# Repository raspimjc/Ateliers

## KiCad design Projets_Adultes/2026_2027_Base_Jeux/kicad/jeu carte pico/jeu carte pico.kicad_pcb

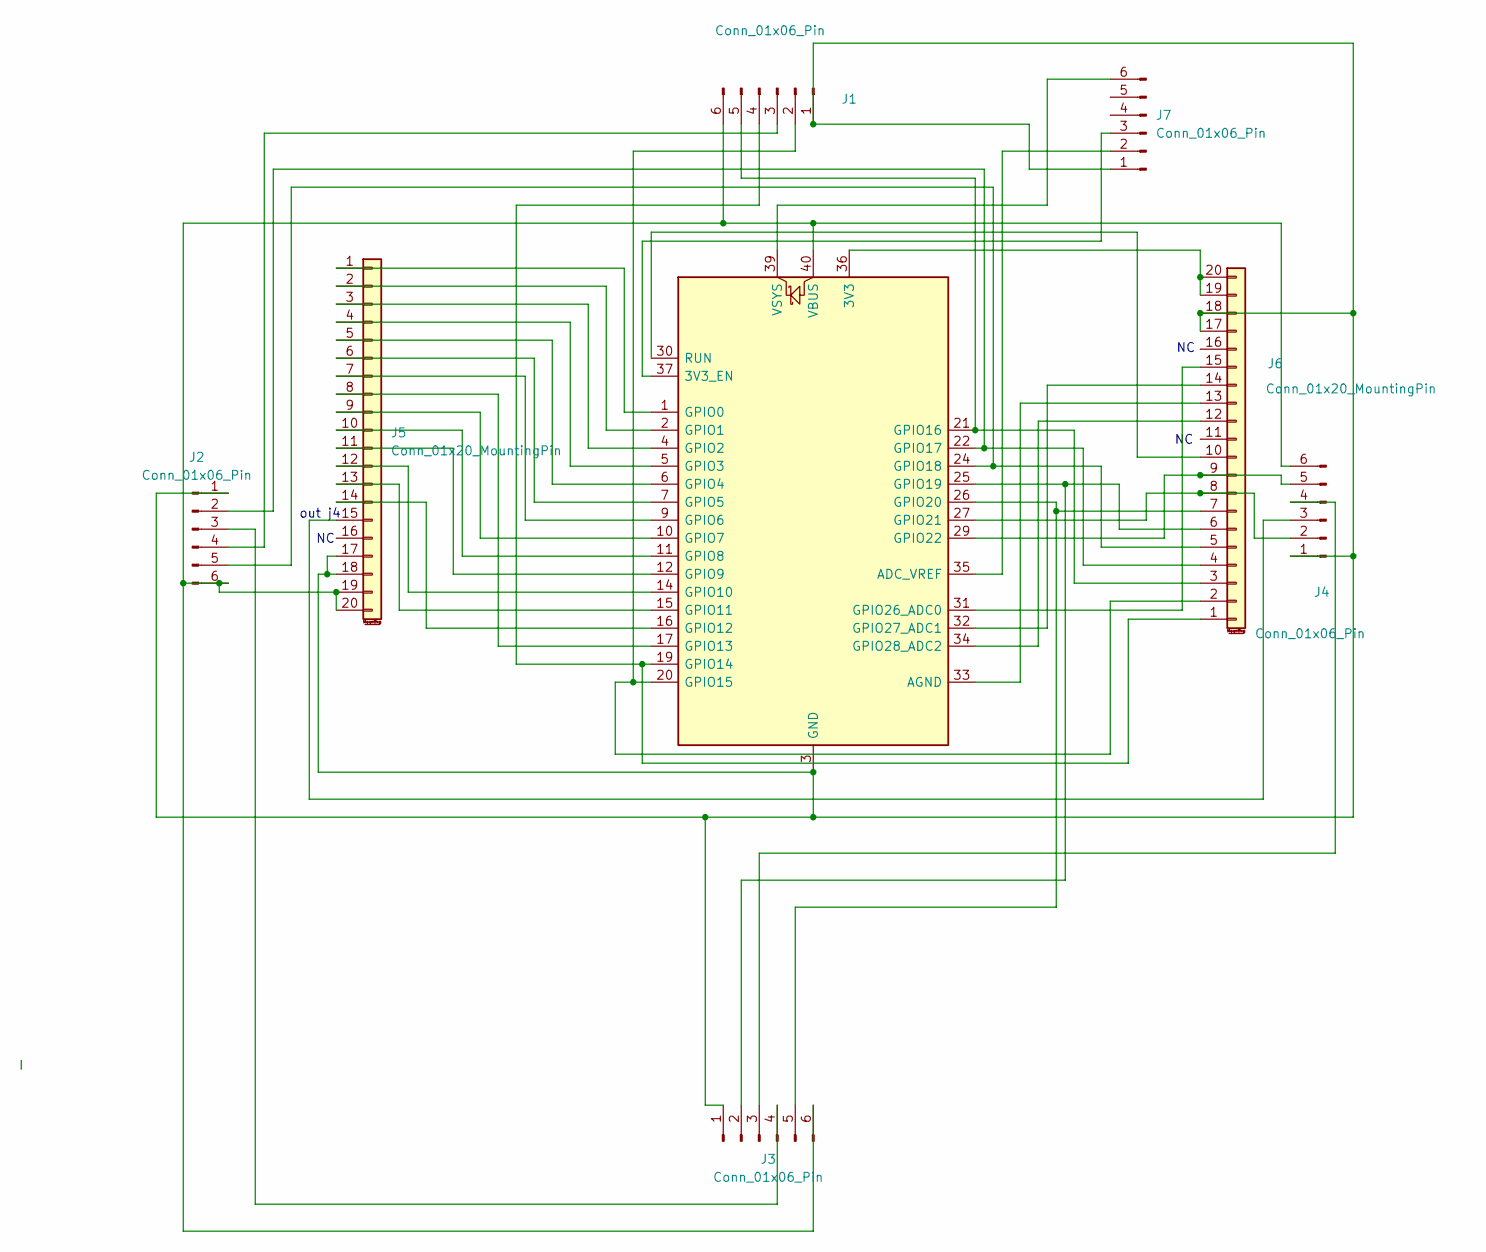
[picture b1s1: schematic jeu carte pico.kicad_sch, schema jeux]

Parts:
A1: RaspberryPi_Pico; Pico_Common_THT
J1, J2, J3, J4, J7: Conn_01x06_Pin; JST_XH_B6B-XH-A_1x06_P2.50mm_Vertical
J5, J6: Conn_01x20_MountingPin

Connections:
unnamed: A1.36 (3V3), J6.19 (Pin_2), J6.20 (Pin_1)
unnamed: A1.37 (3V3_EN), J7.3
unnamed: A1.35 (ADC_VREF), J7.2
unnamed: A1.33 (AGND), J6.13 (Pin_8)
unnamed: A1.1 (GPIO0), J5.1
unnamed: A1.2 (GPIO1), J5.2
unnamed: A1.4 (GPIO2), J5.3
unnamed: A1.5 (GPIO3), J5.4
unnamed: A1.6 (GPIO4), J5.5
unnamed: A1.7 (GPIO5), J5.6
unnamed: A1.9 (GPIO6), J5.7
unnamed: A1.10 (GPIO7), J5.9
unnamed: A1.11 (GPIO8), J5.10
unnamed: A1.12 (GPIO9), J5.11
unnamed: A1.14 (GPIO10), J5.12
unnamed: A1.15 (GPIO11), J5.13
unnamed: A1.16 (GPIO12), J5.14
unnamed: A1.17 (GPIO13), J5.8
unnamed: A1.19 (GPIO14), J1.4, J6.1 (Pin_20)
unnamed: A1.20 (GPIO15), J1.2, J6.2 (Pin_19)
unnamed: A1.21 (GPIO16), J1.5, J6.3 (Pin_18)
unnamed: A1.22 (GPIO17), J2.2, J6.4 (Pin_17)
unnamed: A1.24 (GPIO18), J2.5, J6.5 (Pin_16)
unnamed: A1.25 (GPIO19), J3.2, J6.6 (Pin_15)
unnamed: A1.26 (GPIO20), J3.5, J6.7 (Pin_14)
unnamed: A1.27 (GPIO21), J4.2, J6.8 (Pin_13)
unnamed: A1.29 (GPIO22), J4.5, J6.9 (Pin_12)
unnamed: A1.31 (GPIO26_ADC0), J6.15 (Pin_6)
unnamed: A1.32 (GPIO27_ADC1), J6.14 (Pin_7)
unnamed: A1.34 (GPIO28_ADC2), J6.12 (Pin_9)
unnamed: A1.30 (RUN), J6.10 (Pin_11)
unnamed: A1.40 (VBUS), J1.6, J2.6, J3.6, J4.6, J5.19, J5.20
unnamed: A1.39 (VSYS), J7.6
unnamed: A1.3 (GND), A1.8 (GND), A1.13 (GND), A1.18 (GND), A1.23 (GND), A1.28 (GND), A1.38 (GND), J1.1, J2.1, J3.1, J4.1, J5.17, J5.18, J6.17 (Pin_4), J6.18 (Pin_3), J7.1
unnamed: J1.3, J2.4
unnamed: J2.3, J3.4
unnamed: J3.3, J4.4
unnamed: J4.3, J5.15

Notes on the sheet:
out j4

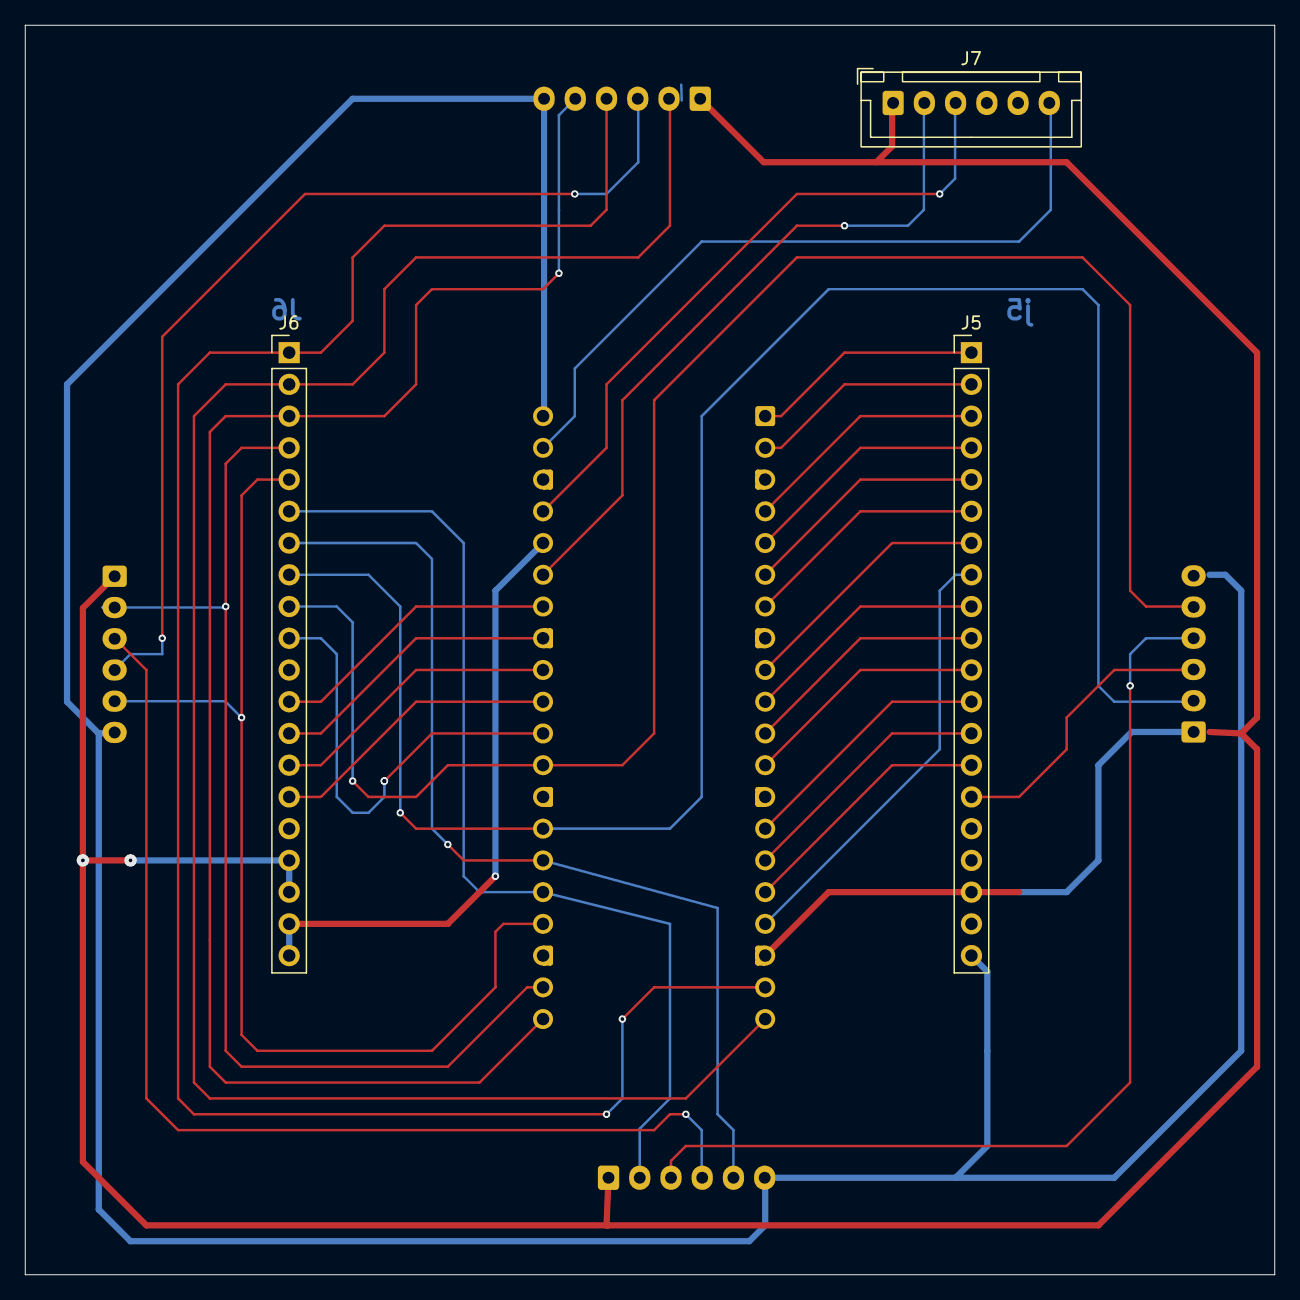
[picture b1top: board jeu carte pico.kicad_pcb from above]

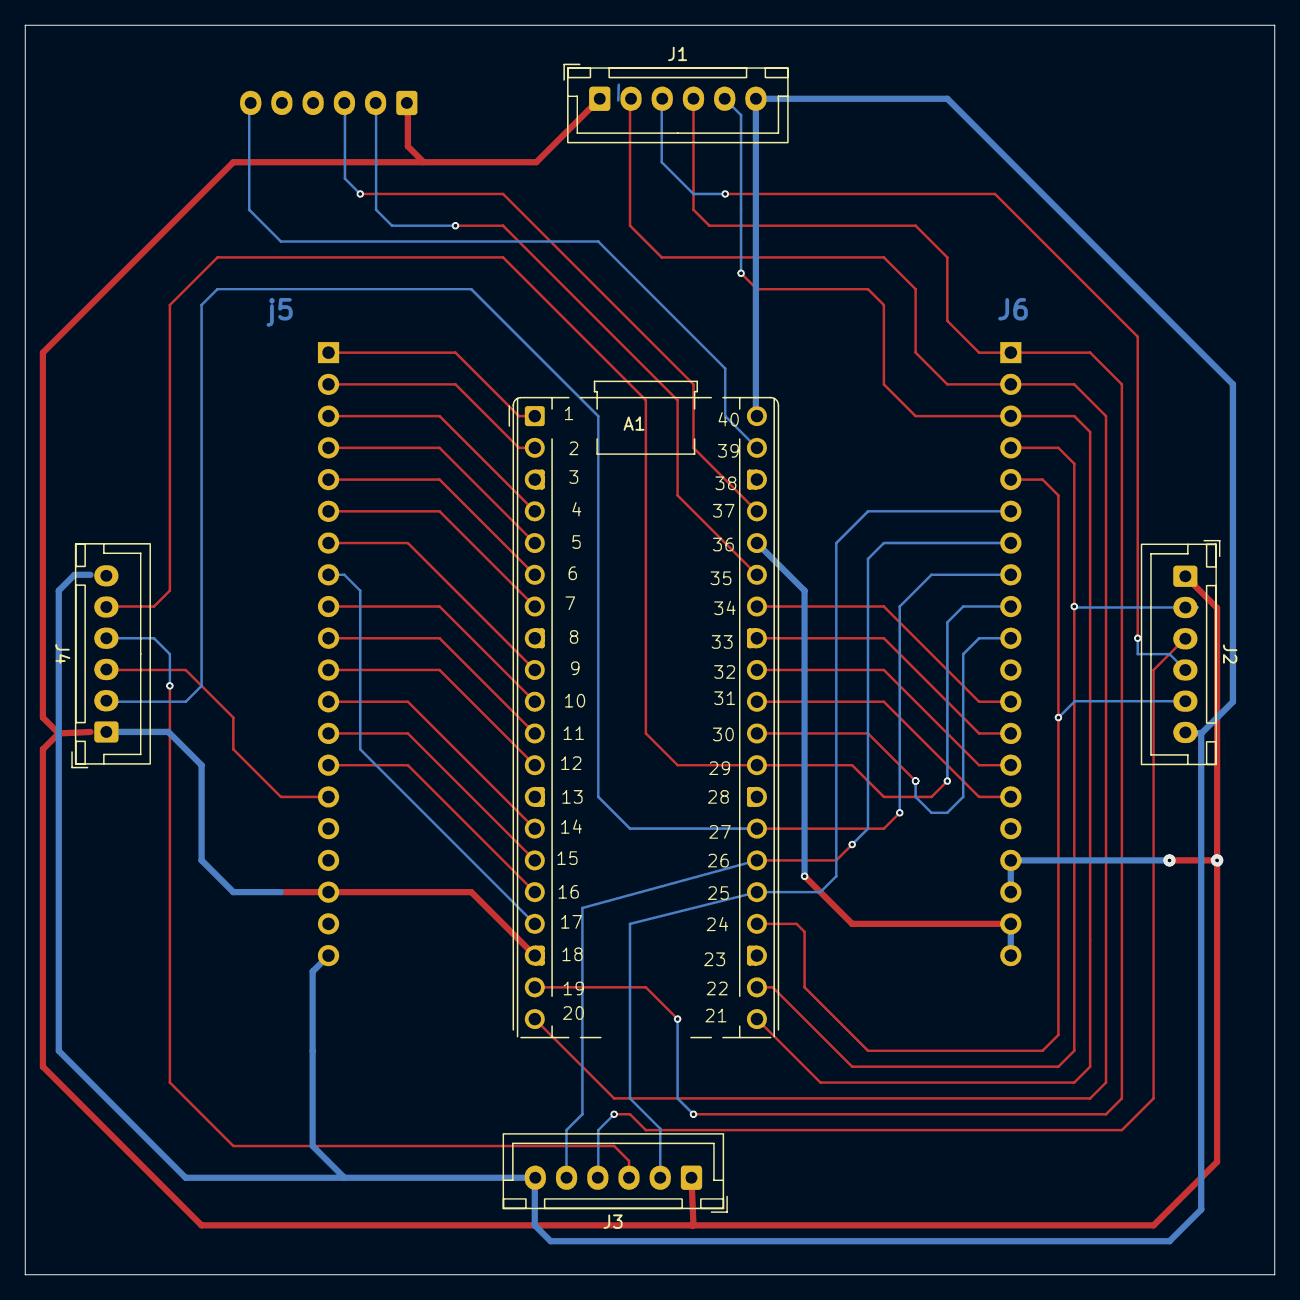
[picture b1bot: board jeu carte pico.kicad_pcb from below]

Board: 2 copper layers, 100.0 x 100.0 mm, 8 parts (5 on the bottom side), 38 nets.

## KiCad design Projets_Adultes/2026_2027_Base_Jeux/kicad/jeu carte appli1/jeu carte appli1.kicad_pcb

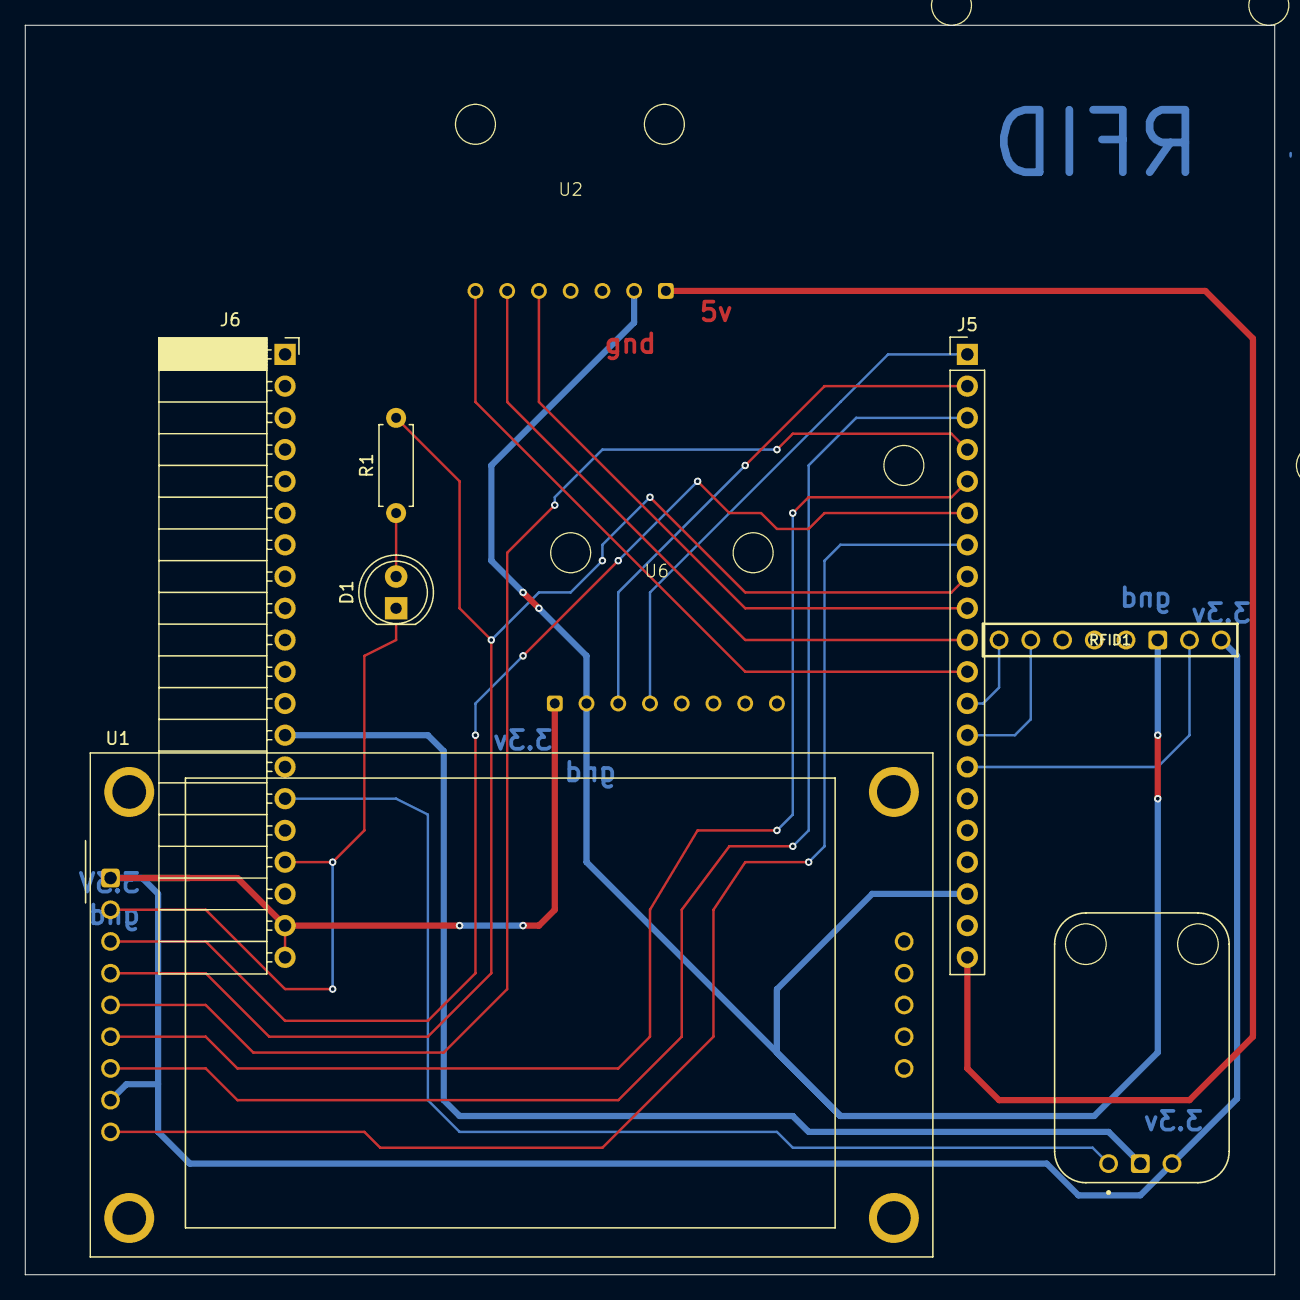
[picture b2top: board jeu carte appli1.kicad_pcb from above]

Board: 2 copper layers, 100.0 x 100.0 mm, 9 parts (0 on the bottom side), 20 nets.

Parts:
D1: LED_Small; LED_D5.0mm
J5: Conn_01x20_Socket_power; PinHeader_1x20_P2.54mm_Vertical
J6: Conn_01x20_Socket_power; PinSocket_1x20_P2.54mm_Horizontal
R1: R_Small; R_Axial_DIN0207_L6.3mm_D2.5mm_P7.62mm_Horizontal
RFID1: RFID-RC522
U1: CR2013-MI2120 tft2.8p; CR2013-MI2120
U2: MAX98357A; i2s
U4: 1063 max4466; MODULE_1063
U6: MPU-6050; gyro

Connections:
unnamed: D1.2 (A), R1.2
unnamed: D1.1 (K), J5.17, J5.18, RFID1.3 (GND), U1.2 (GND), U2.2 (GND), U6.2 (GND)
unnamed: J5.1, U6.4 (SDA)
unnamed: J5.2, U6.3 (SCL)
unnamed: J5.3, U1.7 (SCK)
unnamed: J5.4, U1.5 (D/~C)
unnamed: J5.5, U1.6 (MOSI)
unnamed: J5.6, U1.3 (~CS)
unnamed: J5.7, U1.9 (MISO)
unnamed: J5.8, R1.1, U1.4 (RESET)
unnamed: J5.9, U2.5 (DIN)
unnamed: J5.10, U2.6 (BCLK)
unnamed: J5.11, U2.7 (LRCLK)
unnamed: J5.12, RFID1.8 (SDA)
unnamed: J5.13, RFID1.7 (SCK)
unnamed: J5.14, RFID1.2 (RST)
unnamed: J5.19, J5.20, U2.1 (vdd)
unnamed: J6.13, U4.2 (GND)
unnamed: J6.15, U4.3 (OUT)
unnamed: J6.19, J6.20, RFID1.1 (3V3), U1.1 (VCC), U1.8 (LED), U4.1 (VCC), U6.1 (VDD)

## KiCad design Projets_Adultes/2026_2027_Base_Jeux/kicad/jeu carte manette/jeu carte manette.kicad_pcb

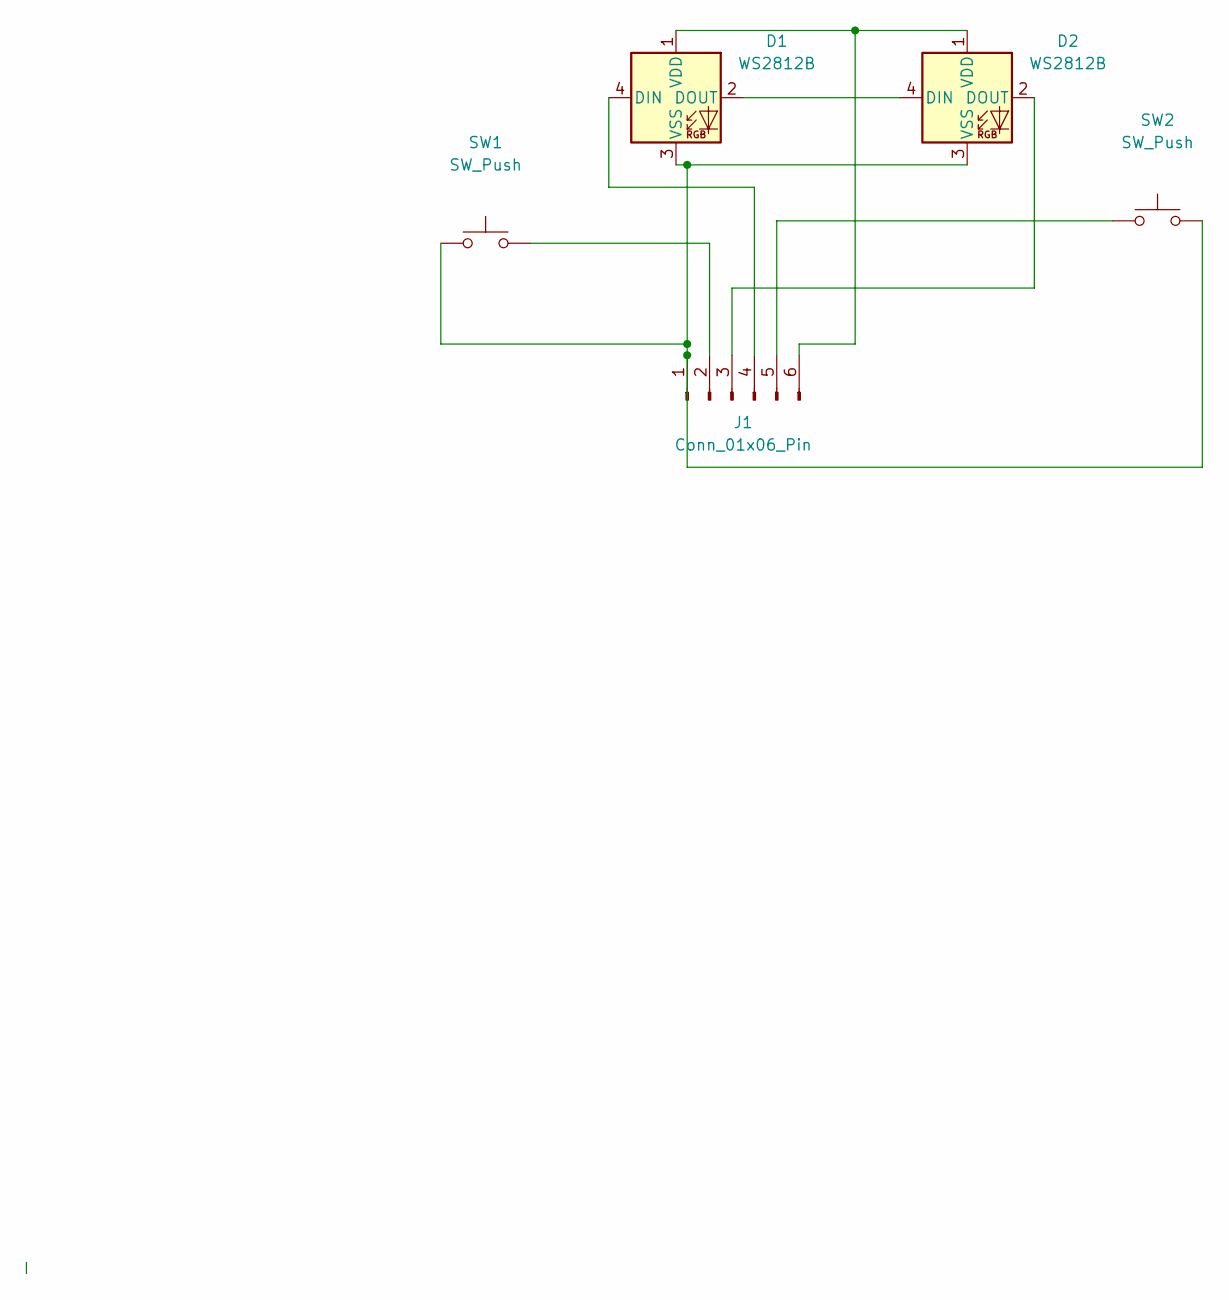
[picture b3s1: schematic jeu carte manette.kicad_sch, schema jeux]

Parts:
D1, D2: WS2812B; LED_WS2812B_PLCC4_5.0x5.0mm_P3.2mm
J1: Conn_01x06_Pin; JST_XH_B6B-XH-A_1x06_P2.50mm_Vertical
SW1, SW2: SW_Push; SW_Cherry_MX_ISOEnter_Plate

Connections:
unnamed: D1.4 (DIN), J1.4
unnamed: D1.2 (DOUT), D2.4 (DIN)
unnamed: D1.1 (VDD), D2.1 (VDD), J1.6
unnamed: D1.3 (VSS), D2.3 (VSS), J1.1, SW1.1, SW2.2
unnamed: D2.2 (DOUT), J1.3
unnamed: J1.2, SW1.2
unnamed: J1.5, SW2.1

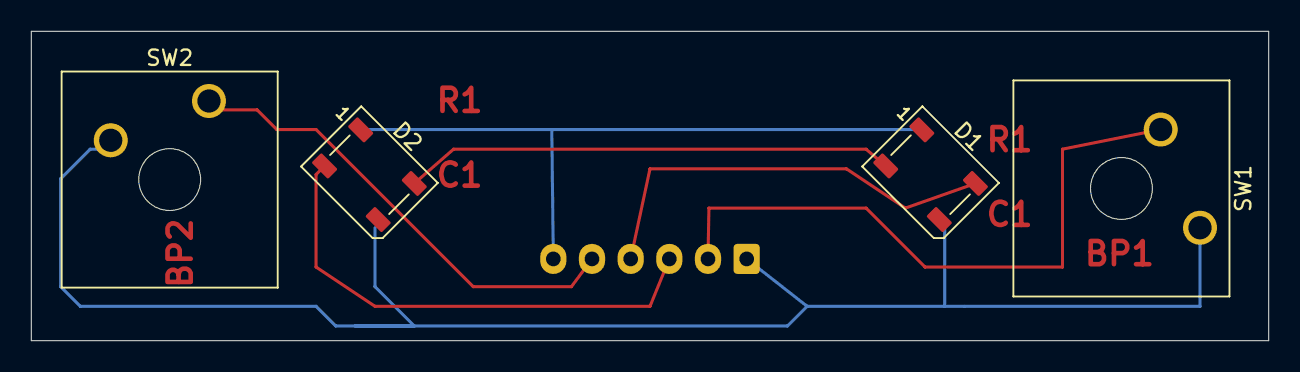
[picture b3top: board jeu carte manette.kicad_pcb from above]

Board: 2 copper layers, 80.0 x 20.0 mm, 5 parts (1 on the bottom side), 7 nets.
